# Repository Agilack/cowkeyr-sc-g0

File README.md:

Cowkeyr Smartcard G0
====================

Cowkeyr is a family of security and access control tools. The goal of SC-G0
project is to design a smartcard reader with an opensource and auditable
firmware.

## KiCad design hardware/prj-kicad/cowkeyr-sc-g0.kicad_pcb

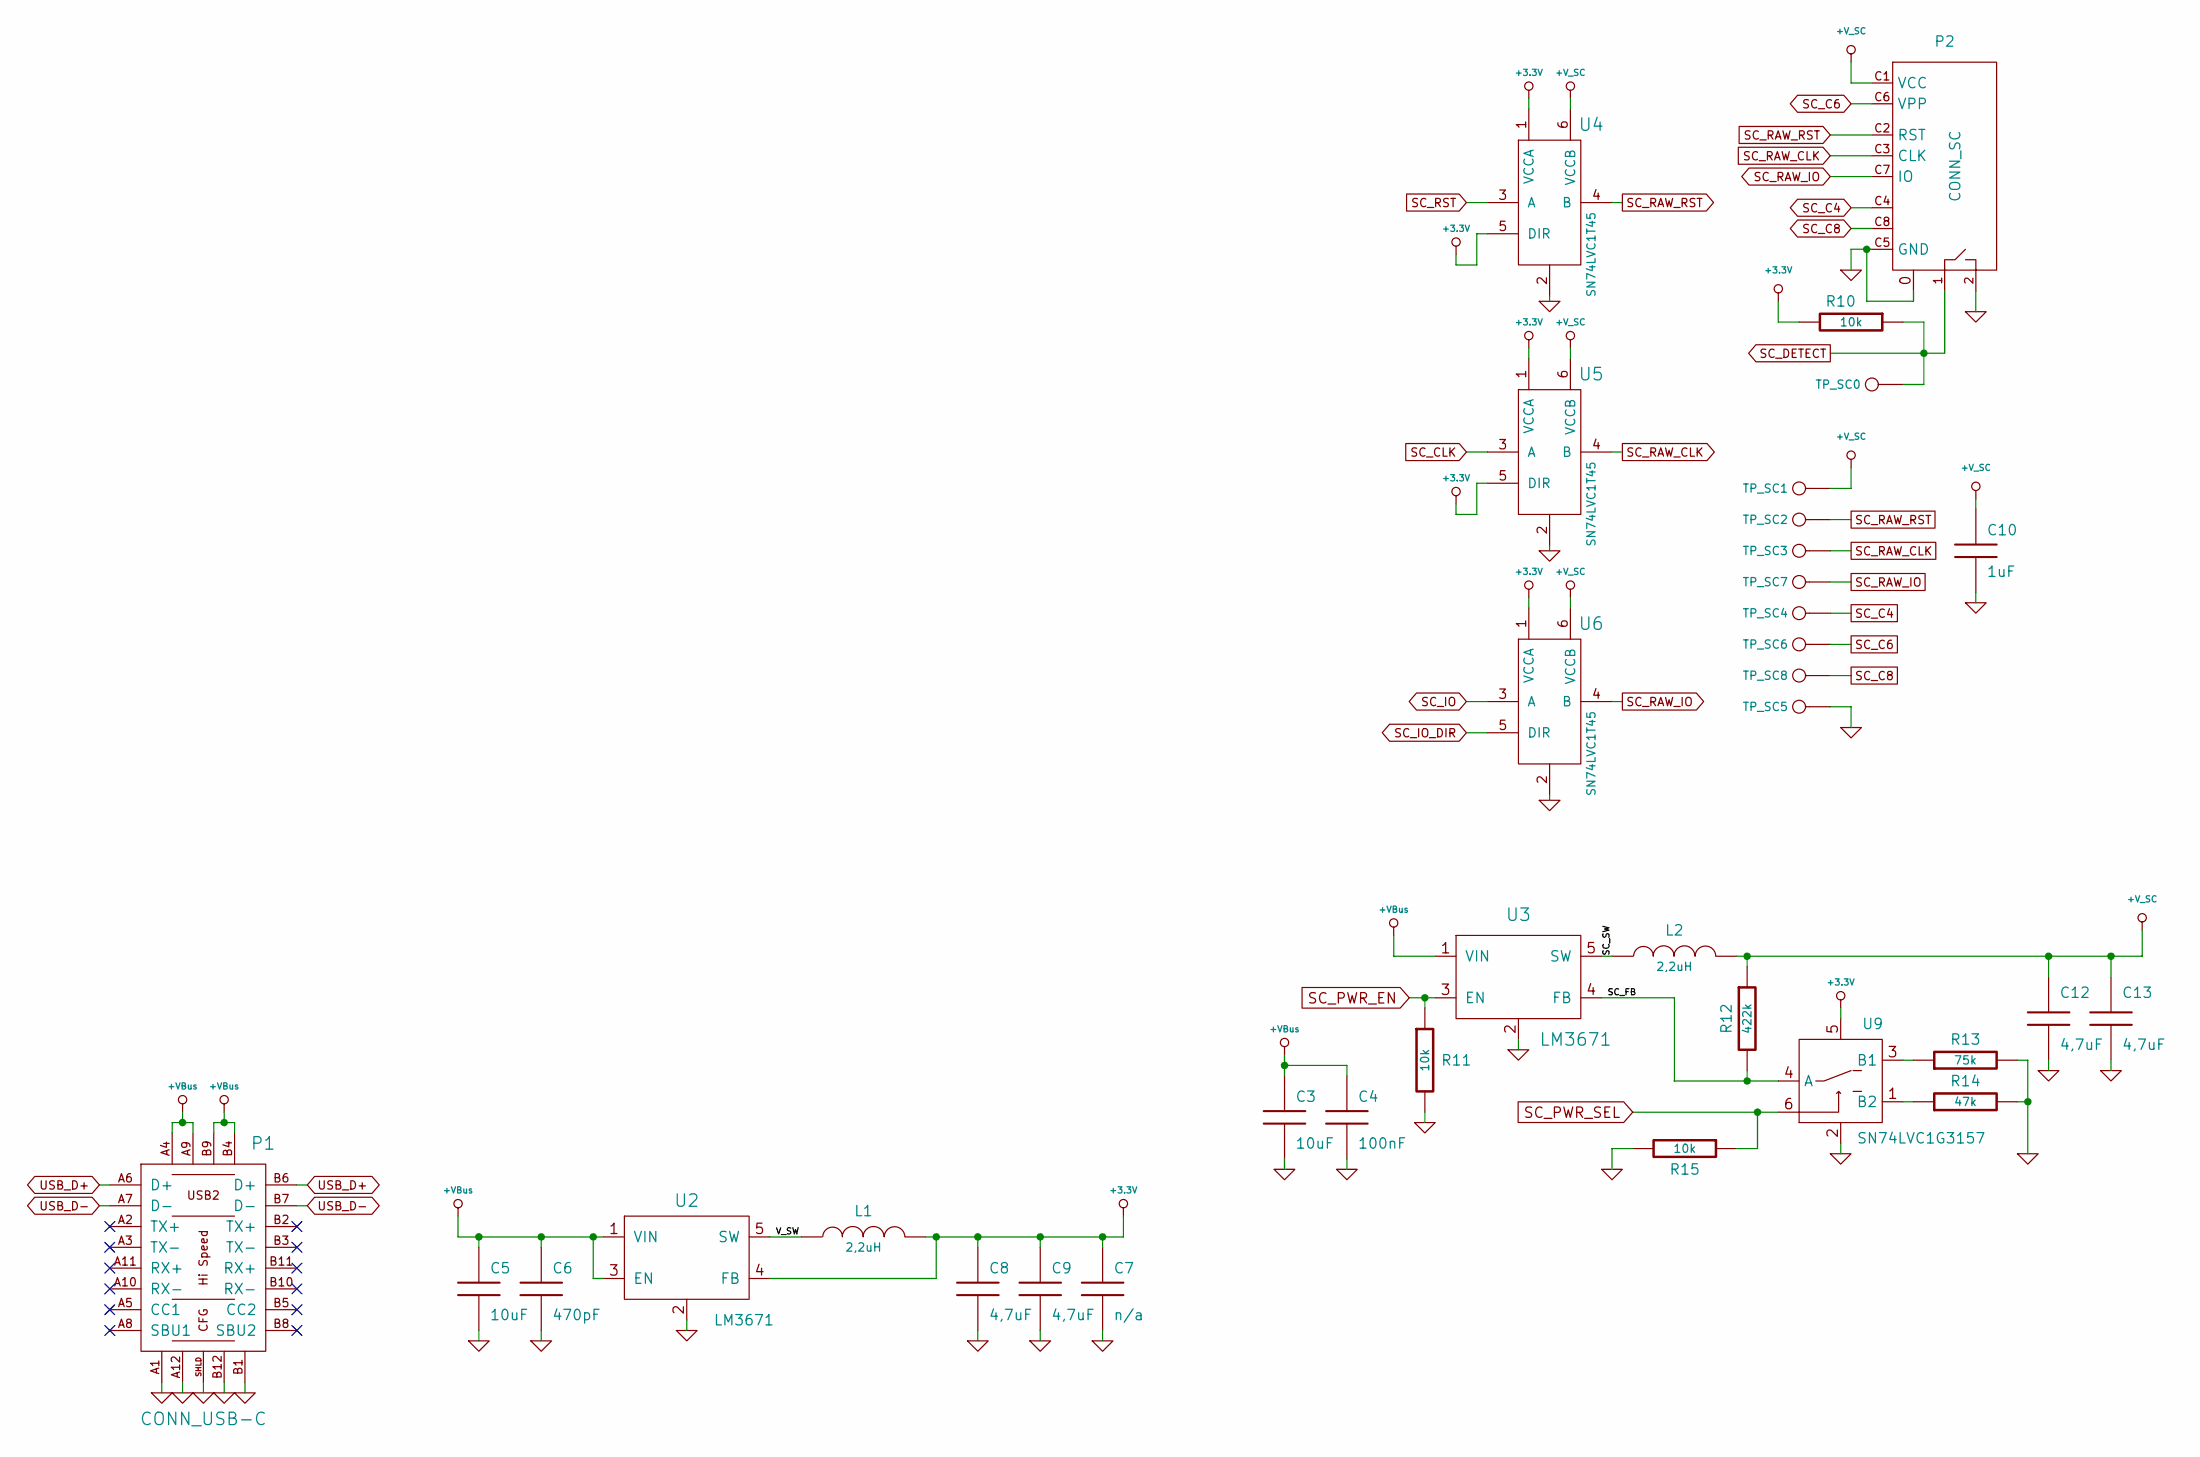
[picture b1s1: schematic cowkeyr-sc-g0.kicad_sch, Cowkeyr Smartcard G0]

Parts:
C3, C5: 10uF; SMD0805
C4: 100nF; SMD0603
C6: 470pF; SMD0603
C7: n/a; SMD1210
C8, C9, C12, C13: 4,7uF; SMD0603
C10: 1uF; SMD0603
L1, L2: 2,2uH; I_CDRH2D14
P1: CONN_USB-C; CONN_632723300011
P2: CONN_SC; CONN_CCM01-25xx
R10, R11, R15: 10k; SMD0603
R12: 422k; SMD0603
R13: 75k; SMD0603
R14: 47k; SMD0603
TP_SC0, TP_SC1, TP_SC2, TP_SC3, TP_SC4, TP_SC5, TP_SC6, TP_SC7, TP_SC8: CONN_1; TP_PIN
U2, U3: LM3671; SOT23-5
U4, U5, U6: SN74LVC1T45; SOT23-6
U9: SN74LVC1G3157; SOT23-6

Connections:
+3.3V: C7.1, C8.1, C9.1, L1.2, R10.2, U2.4 (FB), U4.1 (VCCA), U4.5 (DIR), U5.1 (VCCA), U5.5 (DIR), U6.1 (VCCA), U9.5
+V_SC: C10.1, C12.1, C13.1, L2.2, P2.C1 (VCC), R12.1, TP_SC1.1, U4.6 (VCCB), U5.6 (VCCB), U6.6 (VCCB)
/SC_FB: R12.2, U3.4 (FB), U9.4 (A)
/SC_SW: L2.1, U3.5 (SW)
/V_SW: L1.1, U2.5 (SW)
GND: C3.2, C4.2, C5.2, C6.2, C7.2, C8.2, C9.2, C10.2, C12.2, C13.2, P1.A1, P1.A12, P1.B1, P1.B12, P1.SHLD, P2.0, P2.2, P2.C5 (GND), R11.2, R13.2, R14.2, R15.2, TP_SC5.1, U2.2, U3.2, U4.2, U5.2, U6.2, U9.2
unnamed: R13.1, U9.3 (B1)
unnamed: R14.1, U9.1 (B2)
SC_C4: P2.C4, TP_SC4.1
SC_C6: P2.C6 (VPP), TP_SC6.1
SC_C8: P2.C8, TP_SC8.1
SC_CLK: U5.3 (A)
SC_DETECT: P2.1, R10.1, TP_SC0.1
SC_IO: U6.3 (A)
SC_IO_DIR: U6.5 (DIR)
SC_PWR_EN: R11.1, U3.3 (EN)
SC_PWR_SEL: R15.1, U9.6
SC_RAW_CLK: P2.C3 (CLK), TP_SC3.1, U5.4 (B)
SC_RAW_IO: P2.C7 (IO), TP_SC7.1, U6.4 (B)
SC_RAW_RST: P2.C2 (RST), TP_SC2.1, U4.4 (B)
SC_RST: U4.3 (A)
USB_D+: P1.A6 (D+), P1.B6 (D+)
USB_D-: P1.A7 (D-), P1.B7 (D-)

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
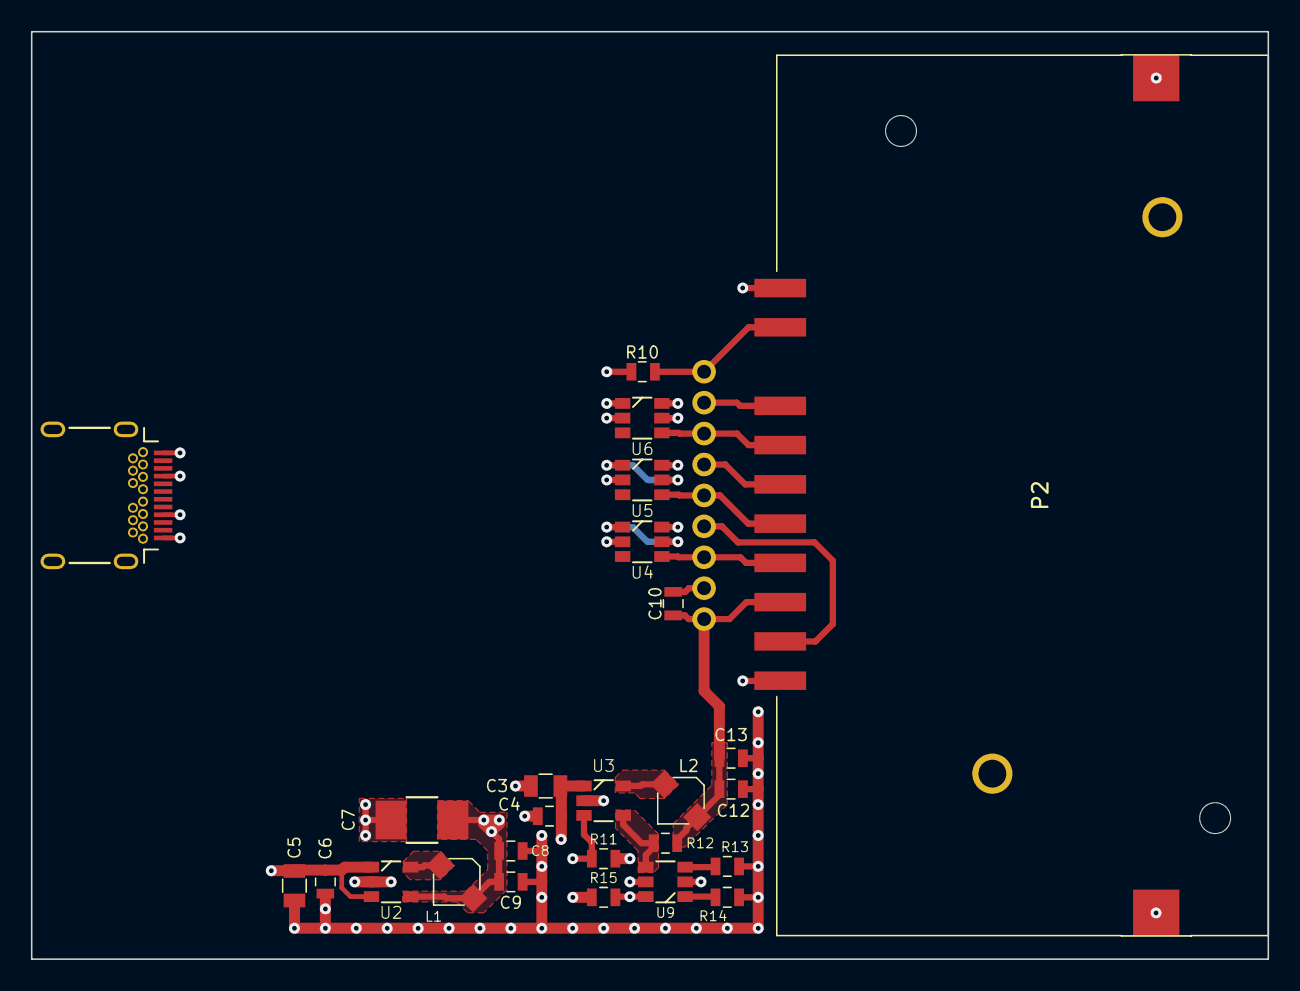
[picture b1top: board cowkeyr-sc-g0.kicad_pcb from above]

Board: 4 copper layers, 80.0 x 60.0 mm, 35 parts (0 on the bottom side), 20 nets.

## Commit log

2023-03-07 --=={ Create project }==--
2023-03-08 HW: Insert SmartCard connector (sch + footprint)
2023-03-09 HW: Replace smartcard connector (bad size) and add power supplies

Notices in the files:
hardware/prj-kicad/cowkeyr-sc-g0.kicad_pcb:
License: CC-by-SA
